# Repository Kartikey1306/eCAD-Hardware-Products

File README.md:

# eCAD Hardware Products

Hardware / PCB CAD design collection for the **EmbeddedOS (EoS)** ecosystem.
The repository organizes hardware product designs by application domain. Each
domain holds one or more product lines, and each product line typically carries
a product datasheet, a bill of materials (`bom.csv`), power-budget simulation
scripts, and placeholder directories for PCB and mechanical CAD artifacts.
Several product lines also include KiCad schematics (`*.kicad_sch`).

> Status varies by design. Directories are at different maturity levels (many
> "Design" / "Pre-production"); PCB and CAD folders often contain `.gitkeep`
> placeholders rather than finished layouts. Check each design's own `README.md`
> and `docs/` for its current state.

## Domains

The repository contains **16** domain design collections:

| Domain | Focus |
|---|---|
| `eAerospace_CAD_Design` | Aircraft components, avionics, UAV/drone systems, space systems |
| `eConsumer_CAD_Design` | Smart home devices, personal wearables, AR/smart devices |
| `eCybersecurity_CAD_Design` | Security appliances and physical security systems |
| `eDefense_CAD_Design` | Surveillance, tactical communications, protection equipment |
| `eElectronics_CAD_Design` | PCBs, embedded controllers, RF modules, FPGAs, AI accelerators |
| `eEnergy_CAD_Design` | Battery products, renewable energy systems, power electronics |
| `eHealth365_CAD_Design` | Two-device health monitoring system (smart patch / smart ring) |
| `eIndustrial_CAD_Design` | Sensors, industrial electronics, infrastructure equipment |
| `eMedical_CAD_Design` | Diagnostic, surgical, patient-care, laboratory equipment |
| `eMining_CAD_Design` | Autonomous mining/construction equipment, industrial safety systems |
| `ePAM_CAD_Design` | Personal air/ground mobility — solar-hybrid transport, 4-product line |
| `eRadar360_CAD_Design` | 360° automotive safety radar + laser + V2X + AI threat detection |
| `eRobotics_CAD_Design` | Industrial robots, autonomous systems, robot components |
| `eSmartCity_CAD_Design` | Urban infrastructure, utilities, telecommunications |
| `eTransport_CAD_Design` | Automotive electronics, rail systems, maritime systems |
| `eosHealth_CAD_Design` | Four-device wearable health platform |

Plus:

- `future_designs/` — early/prospective concepts (e.g. `eBCI-Lite`)
- `docs/` — repository-level documentation

## Typical design layout

Most domains follow a common structure, for example:

```
eAerospace_CAD_Design/
  README.md
  docs/                      business_plan.md, regulatory_path.md
  ebuild_simulation/         eBuild simulation notes
  <product_line>/
    product_datasheet.md
    bom.csv
    simulation/power_budget_sim.py
    hardware/
      pcb/  cad/  antenna/   (artifact folders; often .gitkeep placeholders)
```

Artifact formats present in the repo include Markdown datasheets, CSV BOMs,
Python simulation scripts, and KiCad schematics (`*.kicad_sch`). Some product
lines also include TypeScript/Dart companion app sources and 3D-model notes.

## Simulations

Power-budget simulations are plain Python scripts, runnable per product line:

```bash
cd eAerospace_CAD_Design/<product_line>/simulation/
python3 power_budget_sim.py
```

Design docs reference the [EoSim](https://github.com/embeddedos-org/EoSim)
digital-twin platform for hardware-in-the-loop testing. Running one script alone
does not establish that a product is validated.

## Evidence-backed product validation

The committed `tools/catalog/product_inventory.json` is the complete product
execution set. The v1 contract schemas and policy requirements are documented in
`docs/hardware-validation-contract-v1.md`.

Discover inventory drift and inspect local tool capabilities:

```bash
python3 tools/validate_products.py discover
python3 tools/validate_products.py capabilities
```

Execute V0-V4 for every inventoried product and write hash-bound receipts:

```bash
python3 tools/validate_products.py validate \
  --all \
  --output /tmp/ecad-validation \
  --mode evidence
python3 tools/validate_products.py verify-bundle \
  /tmp/ecad-validation/bundle.json
```

`--mode evidence` succeeds when the selected inventory was executed and valid
receipts were written. Individual products may still be honestly `FAIL`,
`BLOCKED`, `INCONCLUSIVE`, or `NOT_RUN`. Use `--mode gate` for a release check;
it succeeds only when every selected product has real `PASS` evidence for V0,
V1, V2, V3, and V4. Historical baseline entries never waive a failed or missing
requirement.

## CAD dataset and engineering model

`datasets/cad/` holds CAD dataset items for the multi-domain validation work
in issue #27. Each item is a STEP design, the design intent the CAD cannot
carry, and machine-readable requirements; the pipeline extracts it with the
OpenCASCADE kernel, builds an engineering model in which every value states
its source and status, and runs V0-V4 with domain simulators. `UNKNOWN`
values are never filled in: a requirement that depends on one is `BLOCKED`.

```bash
python3 -m pip install -r tools/requirements.txt -r tools/requirements-cad.txt
python3 tools/cad_dataset.py check    datasets/cad/robotic_joint_001
python3 tools/cad_dataset.py validate datasets/cad/robotic_joint_001 --output /tmp/joint-run
```

See [datasets/cad/README.md](datasets/cad/README.md) and
[docs/cad-dataset-engineering-model-v1.md](docs/cad-dataset-engineering-model-v1.md).

## License

MIT — see [LICENSE](LICENSE).

One exception: the EmbeddedOS original boards in [boards/eos](boards/eos), their design
files and the footprint library drawn for them are Copyright (c) 2026 Kartikeydheer Srivastava,
all rights reserved, and are not under the MIT licence. The exact files are listed in
[boards/eos/README.md](boards/eos/README.md#licence).

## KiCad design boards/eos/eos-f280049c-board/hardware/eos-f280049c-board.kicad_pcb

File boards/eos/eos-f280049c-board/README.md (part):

# EoS F280049C Board

A development board for the TI TMS320F280049C (C2000 real-time MCU, LQFP-100) with two
BoosterPack-compatible (40-pin) sites, 58.42 × 156.21 mm, four layers.
Designed by Kartikeydheer Srivastava. All rights reserved: not open source, and not under this repository's MIT licence.
Anyone may view it, clone this repository and run its tests; anything more needs
Kartikeydheer Srivastava's written permission (kartikeydheer@gmail.com). EmbeddedOS (EoS) Research Foundation has a limited, revocable
permission. See [LICENSE.txt](LICENSE.txt) and [the licence summary](../README.md#licence).

A board for the same job as TI's LAUNCHXL-F280049C LaunchPad; an original design, not a copy: no
file of the vendor's was used. "BoosterPack" names TI's plug-in module format to say which modules
fit (nominative use); this board is not a TI product. No design file of the vendor's was used; the header positions come from TI's BoosterPack Pinout Standard (updated Sept 1, 2013) and the 40-pin figure of TI's
BoosterPack Standards and Design Guide (processors.wiki.ti.com, archived 2017-11-03). TI's design
guide SPRACZ9A reproduces one circuit of the LaunchPad (its Figure 3-5, a CAN transceiver); that
figure was not used, and this board has no CAN transceiver. Every circuit value comes from the
chip makers' data sheets listed below.

| | |
|---|---|
|  |  |

## What is on it

| Block | What and why | Source |
|---|---|---|
| TMS320F280049C | C28x at 100 MHz with FPU, TMU and CLA, 256 KB flash, three 12-bit ADCs, LQFP-100 (PZ). KiCad's `LQFP-100_14x14mm_P0.5mm` footprint: TI's PZ0100A drawing gives a 14 × 14 mm body, 15.8–16.2 mm across the leads, 0.5 mm pitch, 1.6 mm maximum height (JEDEC MS-026) and 1.5 × 0.3 mm example pads on a 15.4 mm row pitch; KiCad's 1.6 × 0.3 mm pads on 15.35 mm cover that land. Turned 270° so its analog pins face both sites' analog header pins and its GPIO sides face the right-hand headers and the bottom. | TI SPRS945H (data sheet), Table 5-1, Figure 5-1, PZ0100A |
| Core supply | Internal VREG: VREGENZ tied straight to VSS, so a single 3.3 V supply runs the chip; the guide calls this the cost-effective choice for a small board. The internal DC-DC is not used (it needs a 2.2 µH inductor and 20 µF on VDDIO_SW, costs GPIO22/23, and the guide warns of ADC noise). 4.7 µF X7R 25 V 1206 (Murata GRM31CR71E475KA88L) at each of the four VDD pins: 18.8 µF nominal, with the modeled effective-capacitance margin described below; CVDD = 12–27 µF total and 0.1–6.75 µF per pin ("Configuration 1"); each VDD pin with its capacitor is its own net, which the data sheet allows in internal VREG mode. | SPRS945H 6.9.1.2.4–6.9.1.2.6, 6.9.1.3.1.2, 6.9.1.4.1, 6.9.1.5.1; TI SPRACZ9A 3.4.3 |
| 3.3 V pins | VDDIO, VDDA and VDDIO_SW on one 3.3 V rail, the inner layer 2 plane ("strongly recommended"; a separate VDDA "typically offers minimal benefits"). 0.1 µF at each VDDIO pin and at VDDIO_SW, 2.2 µF at each VDDA pin to VSSA. VSS_SW to VSS. | SPRS945H 6.9.1.4.1, 6.9.1.5.1, Table 5-1 |
| ADC references | Internal reference mode: 4.7 µF X7R 25 V 1206 (GRM31CR71E475KA88L) from VREFHIA (pin 25) to VREFLOA (pin 27) and from VREFHIB/C (pin 24) to VREFLOB/C (pin 26), at the chip's corner, each joined to both pins before the autorouter runs. Nothing else loads VREFHI. One ground plane (inner layer 1) for VSS and VSSA, since the analog lines arrive from header pins and a clean split is not possible. | SPRS945H Table 5-1; SPRACZ9A 3.3.3, 4.5 |
| 20 MHz clock | SiTime SiT8008BI-22-33N-20.000000E, a 3.3 V CMOS oscillator (±25 ppm with aging and temperature, 45–55 % duty, ≤ 2 ns rise/fall), into X1 in single-ended mode, X2 open, 0.1 µF at its supply. X1 accepts 2–20 MHz from an oscillator with ≤ 6 ns edges and 45–55 % duty. Not the internal oscillators: ±3 % over voltage and temperature, where the guide asks for an external source for CAN and for better than 1 %. Not a crystal: the data sheet asks for a crystal rated ≥ 1 mW of drive (or a damping resistor to be evaluated with the crystal), ESR ≤ 45–50 Ω and a 6–12 pF load at 20 MHz; the stocked SMD crystals with that ESR and load are rated 100 µW, and the 1 mW HC-49 parts are stocked with an 18 pF load, which would need 26–30 pF per side against the 24 pF limit. | SPRS945H 6.9.3.2.1, 6.9.3.4.4, 6.9.3.4.7, 6.9.3.5.1, Figure 6-17, Table 5-10; SPRACZ9A 3.2.4, 3.6.1; SiT8008B data sheet rev 1.08 |
| Reset | 2.2 kΩ pull-up and 100 nF on XRSn (2.2–10 kΩ, ≤ 100 nF so the watchdog can still pull it low in 512 clock cycles), a reset button straight to ground; also on J2.16 and J6.56. | SPRS945H 6.9.2, Figure 6-12, Table 5-1; SPRACZ9A 3.5 |
| Boot mode | GPIO24 (boot pin 1) and GPIO32 (boot pin 0) each have a 10 kΩ pull-up and go to JP1: a shunt on 1-2 pulls GPIO24 to ground through 1 kΩ (0.3 V, under VIL = 0.8 V), on 3-4 GPIO32. No shunt: flash; 1-2: SCI boot through the USB bridge (SCIA on GPIO28/29); 3-4: CAN; both: parallel I/O. Both pins are site B chip selects, which a BoosterPack does not drive, as the guide asks of a boot pin used "as outputs whose state is irrelevant during boot". | SPRS945H Tables 7-13, 7-18, 6.6; SPRACZ9A 3.2.5 |
| JTAG (J10) | TI 14-pin header, 2 × 7 at 0.1 in with pin 6 as the key, in place of TI's on-board XDS110, whose firmware is TI's: 1 TMS (2.2 kΩ pull-up), 3 TDI and 7 TDO (10 kΩ pull-ups; their internal pull-ups are off by default), 11 TCK, 9 RTCK looped to TCK, 4 TDIS and 8/10/12 to ground with no resistor, 5 PD to 3.3 V through 100 Ω, 2 TRST open (the chip has no TRSTn pin), 13/14 EMU0/EMU1 pulled up with 4.7 kΩ. Any XDS-class probe connects here; the header is under 6 in from the chip, so no buffers. | TI XDS Target Connection Guide; TI SPRU655I Figure 4, Table 13; SPRS945H Table 5-1; SPRACZ9A 3.7.1, Figure 3-16 |
| USB-UART (J9) | CP2102N-A02-GQFN20 on SCIA (GPIO28 RX, GPIO29 TX), the default SCI boot pins, on the board's 3.3 V with its regulator unused, so it is powered whenever the MCU is and neither drives an unpowered chip. 4.7 µF + 0.1 µF on VREGIN and on VDD, each 0.1 µF at its pin; 1 kΩ RSTb pull-up; 1 kΩ in TXD and RXD; 10 kΩ pull-up on SCIA_RX. VBUS sense: the self-powered figure's 22.1 kΩ / 47.5 kΩ divider from the fused VBUS plus a 5.1 kΩ bleed, so the pin stays under VIL = 0.6 V unless more than 185 µA is pushed into VBUS; the Schottky's reverse leakage is 0.8 µA typical at 25 °C and about 0.1 mA typical at 85 °C. A guaranteed hot-leakage limit is not supplied, so unplug detection with externally supplied 5 V still needs a temperature test. The main USB pair runs from the receptacle's A6/A7 contacts through the ESD part's pads straight down into the CP2102N's D+/D− pins, on the top layer, laid before the autorouter; the duplicate B6/B7 contacts join afterward, with two vias in the B7 branch. | Silicon Labs CP2102N Rev. 1.5, Figures 2.3, 2.6, section 2.3, Tables 3.2, 3.7, 3.10; SPRS945H Table 7-18; SPRACZ9A 3.2.4; Nexperia PMEG6010CEH v.4 |
| USB ESD, USB-C | Littelfuse SP0503BAHTG at the connector: three TVS diodes to ground on VBUS, D+ and D−, 5.5 V standoff, ≤ 100 nA at 5 V, 30 pF; it has no path from D+/D− into VBUS, so a D+ pull-up left on cannot hold VBUS up after a host leaves. USB-C as a 5 V sink: 5.1 kΩ Rd on CC1 and CC2. | Littelfuse SP05xxBA; CP2102N Figure 2.5; TI SLYY228 p. 54 |
| Power | USB VBUS → 500 mA polyfuse (0.42 A hold at 40 °C) → PMEG6010CEH Schottky → +5V, which feeds both sites' 5 V pins and the AP7361C-33 LDO (1 A, current limit ≥ 1.1 A, 4.7 µF in, 10 µF out). The Schottky stops a BoosterPack that drives 5 V into J3.21 or J7.61 from back-feeding the USB host; that BoosterPack then powers the board. Design allowance for the 3.3 V load: the MCU's 113 mA + 30 mA (IDDIO + IDDA maxima with the internal VREG), the CP2102N 14 mA, the oscillator 4.5 mA, LEDs and pull-ups about 12 mA: about 175 mA, 263 mA with the guide's 1.5 margin, well inside the LDO's 1 A; its minimum current limit exceeds the VREG's 650 mA typical turn-on inrush. Startup under this load has not been measured: the LDO's 150 µs typical startup figure uses a different load and capacitance, so it does not establish the board's ramp rate. Green power LED at 2.1 mA. | SPRS945H 6.5.2, 6.9.1.5.1–6.9.1.5.2; SPRACZ9A 3.4.5; Diodes DS37274 Rev. 5-2; Littelfuse 1206L; Nexperia PMEG6010CEH v.4; Kingbright DSAO7432 |
| Shared power budget | The LDO may carry 300 mA: at 5.25 V in it dissipates 0.59 W, 64 °C above ambient at 110 °C/W. So the BoosterPacks may take 125 mA from the 3.3 V pins (J1.1 and J5.41 together). In all, the board takes up to 0.38 A from USB: 175 mA for itself, 200 mA for the BoosterPacks' 3.3 V and 5 V pins together (no more than 125 mA of it on 3.3 V), 1 mA for the bleed: under the polyfuse's 0.42 A hold at 40 °C and a configured 500 mA USB supply. This thermal budget does not establish USB attach or suspend compliance. At 0.38 A and 4.75 V from the host, the fuse (0.70 Ω) and Schottky (≤ 0.53 V) leave ≥ 3.95 V on +5V: the LDO keeps regulating, but the 5 V pins carry 3.95–4.9 V, not a regulated 5 V. The Schottky then dissipates ≤ 0.2 W, 66 °C above ambient on its standard footprint. J1.1 and J5.41 are outputs only. | DS37274 (p. 4 absolute maximum, p. 5 θJA, dropout); Littelfuse 1206L derating table; PMEG6010CEH Tables 5–7 |
| User LEDs, buttons | Red LED on GPIO6 (J4.40) and yellow on GPIO14 (J4.39), both PWM outputs, through 680 Ω: 2.3 and 2.1 mA. Buttons on GPIO23 (J2.11/J6.51, 10 kΩ pull-up because of its 45 µA leakage) and GPIO11 (J2.17/J6.57, internal pull-up), each through 1 kΩ because the pins also reach the BoosterPacks; a reset button. | Kingbright DSAO7433, DSAO7434; SPRS945H 6.6, Table 5-1 |
| I2C pull-ups | 2.2 kΩ on SDA and SCL: above RP(min) = 0.97 kΩ, fast mode up to 161 pF. | SPRACZ9A 3.2.4; TI SLVA689A Eq. 1, 6, Table 2-1 |
| BoosterPack headers | Samtec SSW-110-23-F-D, female with long male leads, so the board stays usable under a stack of BoosterPacks. | TI BoosterPack Pinout Standard (Sept 1, 2013) p. 2 |

### BoosterPack pin map

Each site follows TI's 40-pin standard: 0.1 in grid, outer headers 1.8 in apart, inner 1.6 in,
pin-1 rows level. The sites sit one above the other, 2.5 in (63.50 mm) apart, so two BoosterPacks fit at once
(each reaches 350 mil above its pin 1 and 0.15 in below its last row). Site B's headers are named
J5 (as J1), J7 (as J3), J8 (as J4) and J6 (as J2), with pins numbered 40 above site A's. The chip
has 35 GPIOs free for 50 digital positions, so the sites share the buses the standard says can be
shared (SPI and I2C) and some GPIO positions; a shared position joins site A pin n to site B pin
n + 40. Each site keeps its own UART, PWMs and chip selects. Mux positions from data sheet Table 5-6.

| Pin | Standard | Site A | | Pin | Standard | Site B |
|---|---|---|---|---|---|---|
| J1.1 | 3.3 V | +3V3 (output) | | J5.41 | 3.3 V | +3V3 (output) |
| J1.2 | analog | B3 | | J5.42 | analog | B4/C8 |
| J1.3 | UART RX (into the MCU) | GPIO59 / LINA_RX | | J5.43 | UART RX | GPIO13 / SCIB_RX |
| J1.4 | UART TX | GPIO22 / LINA_TX | | J5.44 | UART TX | GPIO12 / SCIB_TX |
| J1.5 | GPIO | GPIO33, shared | | J5.45 | GPIO | GPIO33, shared |
| J1.6 | analog | C0 | | J5.46 | analog | C3 |
| J1.7 | SPI CLK | GPIO56 / SPIA_CLK, shared | | J5.47 | SPI CLK | GPIO56, shared |
| J1.8 | GPIO | GPIO16, shared | | J5.48 | GPIO | GPIO16, shared |
| J1.9 | I2C SCL | GPIO27 / I2CA_SCL, shared | | J5.49 | I2C SCL | GPIO27, shared |
| J1.10 | I2C SDA | GPIO26 / I2CA_SDA, shared | | J5.50 | I2C SDA | GPIO26, shared |
| J3.21 | 5 V | +5V | | J7.61 | 5 V | +5V |
| J3.22 | GND | GND | | J7.62 | GND | GND |
| J3.23–J3.28 | analog | A2, A3, C4, C2, A1/DACB_OUT, A0/DACA_OUT | | J7.63–J7.68 | analog | A9, A8, A4, A5, C1, C5 |
| J3.29, J3.30 | reserved | not connected | | J7.69, J7.70 | reserved | not connected |
| J4.40 | PWM | GPIO6 / EPWM4A (red LED) | | J8.80 | PWM | GPIO3 / EPWM2B |
| J4.39 | PWM | GPIO14 / EPWM8A (yellow LED) | | J8.79 | PWM | GPIO2 / EPWM2A |
| J4.38 | PWM | GPIO9 / EPWM5B | | J8.78 | PWM | GPIO0 / EPWM1A |
| J4.37 | PWM | GPIO5 / EPWM3B | | J8.77 | PWM | GPIO7 / EPWM4B |
| J4.36, J4.35 | timer capture | GPIO31, GPIO17 (eCAP through the Input X-BAR), shared | | J8.76, J8.75 | timer capture | shared |
| J4.34–J4.31 | GPIO | GPIO4, GPIO58, GPIO57, GPIO25, shared | | J8.74–J8.71 | GPIO | shared |
| J2.20 | GND | GND | | J6.60 | GND | GND |
| J2.19 | PWM | GPIO15 / EPWM8B | | J6.59 | PWM | GPIO1 / EPWM1B |
| J2.18 | SPI CS (wireless) | GPIO34 | | J6.58 | SPI CS (wireless) | GPIO40 |
| J2.17 | GPIO** | GPIO11, shared (button SW3) | | J6.57 | GPIO** | shared |
| J2.16 | RST | XRSn | | J6.56 | RST | XRSn |
| J2.15 | SPI MOSI | GPIO8 / SPIA_SIMO, shared | | J6.55 | SPI MOSI | shared |
| J2.14 | SPI MISO | GPIO10 / SPIA_SOMI, shared | | J6.54 | SPI MISO | shared |
| J2.13 | SPI CS (display) | GPIO39 | | J6.53 | SPI CS (display) | GPIO24 (boot pin 1, 10 kΩ pull-up) |
| J2.12 | SPI CS (other) | GPIO30 | | J6.52 | SPI CS (other) | GPIO32 (boot pin 0, 10 kΩ pull-up) |
| J2.11 | GPIO | GPIO23, shared (button SW2) | | J6.51 | GPIO | shared |

Notes for firmware and BoosterPack designers:

- **Clock:** the 20 MHz oscillator drives X1 single-ended: set XTALCR.SE = 1 (data sheet
  Figure 6-17). Keep GPIO19 in input mode with its pull-up disabled (Table 5-1). The chip starts on INTOSC2.
- **Site A's UART is LIN-A** in its SCI-compatible mode (the data sheet lists it as a
  "UART-Compatible Local Interconnect Network"); site B's is SCI-B. SCI-A is the USB bridge.
- **GPIO22** comes out of reset in DC-DC mode: clear its GPAAMSEL bit, with DCDCCTL.DCDCEN left
  at 0, before using it as LINA_TX (Table 5-1).
- **GPIO23** has about 100 pF of internal capacitance and up to 45 µA of leakage (Table 5-1,
  section 6.6): it suits the button and slow signals, not fast edges.
- **Boot pins:** a BoosterPack must not pull J6.53 (GPIO24) or J6.52 (GPIO32) low at reset, or the
  chip boots in another mode. The 10 kΩ pull-ups keep both chip selects high until firmware runs.
- **Shared positions:** a shared GPIO, capture input or bus line reaches both sites; two
  BoosterPacks must not both drive one.
- **The buttons** need GPIO11's internal pull-up enabled (GPIO23 has its own 10 kΩ).
- **Power on the 3.3 V pins (J1.1, J5.41):** outputs only, 125 mA for both sites together; never
  feed them. The 5 V pins may be fed by a BoosterPack (the Schottky keeps that 5 V off USB).
- The analog pins A6, B2/C6, A10, B0, C14 and the PGAx_IN-only pins are not connected
  (Table 5-10 allows it); the five PGAx_GND pins are tied to VSSA.

## Not on this board

- **TI's on-board XDS110 debug probe.** Its firmware is TI's, so it is replaced by the standard TI
  14-pin JTAG header (J10) for an external XDS110, XDS200 or similar probe, and a separate USB-UART
  bridge (CP2102N) for the serial port and SCI boot.
- **A CAN transceiver, and any other interface transceiver.** The CAN lines are free GPIOs; a
  BoosterPack with a transceiver can use CAN-A or CAN-B through the pin mux.
- **A crystal.** An oscillator drives X1 instead (see the clock row above).
- **External 1.2 V supply and the internal DC-DC.** The internal LDO VREG makes the core supply.
- **An external ADC reference.** The chip's internal reference drives VREFHI; the guide's
  external-reference circuit (REF3030 plus an op-amp) is not fitted.
- **Pull resistors on the PWM outputs and on four of the six chip selects.** SPRACZ9A 3.2.1 says
  PWM lines and chip selects "should have external pull-resistors to enforce a state during
  power-up", since the GPIOs float until firmware runs; only GPIO24 and GPIO32 (boot pins, site B
  chip selects) have them here. A BoosterPack whose PWM or chip-select inputs must be held at
  power-up brings its own.
- **ESD parts on the BoosterPack lines:** the headers are a board-to-board connection.
- The vendor schematic, PCB, Gerber and BOM files were not opened. SPRUII7B was used only for published mechanical facts (Table 1 and Figure 12).

## Mechanical compatibility

The outline is 58.42 × 156.21 mm (2300 × 6150 mil), with 1.27 mm (50 mil) corner radii,
from TI SPRUII7B Table 1 and Figure 12. Coordinates below are measured from the upper-left
corner; internal component placement and electrical routing are independently designed.

| Feature | Position |
|---|---|
| Outer BoosterPack columns | x = 6.35 and 52.07 mm (250 and 2050 mil) |
| Inner columns | x = 8.89 and 49.53 mm (350 and 1950 mil) |
| Site A first row | y = 50.80 mm (2000 mil) |
| Site B first row | y = 114.30 mm (4500 mil); 63.50 mm between sites |
| Four mounting-hole centres | 2.54 mm (100 mil) from their two adjacent edges |
| Mounting-hole drill | 3.2 mm non-plated M3 clearance; intentionally 0.152 mm larger than the published 120 mil (3.048 mm) nominal |

The two header patterns and overall footprint match those published dimensions. This is not
an enclosure-fit or plug-stack qualification: the USB-C connector replaces micro-USB, debug
and boot connectors are independently placed, and no physical fit has been tested. The
mounting holes are unplated; M3 heads/washers can overhang the edge, as the 2.54 mm corner
centre offset is smaller than a typical screw-head radius.

## Core and reference capacitor margin

C10/C17/C20/C22 (core) and C14/C15 (references) use Murata GRM31CR71E475KA88L,
4.7 µF ±10 %, X7R, 25 V, 1206. Murata's public SimSurfing model was sampled on 2026-10-15
at 10 mVrms, −40 to +125 °C in 5 °C steps. The core sweep from 0 to 1.375 V gives
4.022–4.562 µF; the more conservative reference sweep from 0 to 3.625 V gives at least
3.898 µF. Applying −10 % initial tolerance and a further 10 % design reserve yields at least
3.258 µF per core pin (13.03 µF total, above the required 12 µF) and 3.157 µF per reference
(above the required 2.2 µF). On the high side, nominal capacitance ×1.10 tolerance ×1.15
X7R variation is 5.946 µF per core pin and 23.78 µF total, below 6.75/27 µF.

These are manufacturer-model results with explicit engineering reserve, not guaranteed
production minima or qualification of the board over that temperature range. Verify the
procured capacitors at operating DC bias, small AC amplitude, temperature and age before
production; the extra 10 % reserve is not a manufacturer aging specification. The internal
reference's settling time with 4.7 µF also needs bring-up verification. VDDA's C13/C16 remain
2.2 µF nominal: SPRS945H 6.9.1.5.1 gives CVDDA as **typical**, whereas Table 5-1 explicitly
requires **at least** 2.2 µF at VREFHI. The earlier 0603 core and nominal 2.2 µF reference
choices were replaced because they did not demonstrate the required effective minimum.

## Build results

The numbers below are from `build-report.json` and `drc.json` in this folder.

| Check | Result |
|---|---|
| Schematic ERC | 0 violations |
| DRC errors | 0 |
| Unconnected items | 0 |
| Schematic ↔ board parity | 0 differences |
| DRC warnings | 2: silkscreen within the board-edge clearance, the outline of J9 (USB-C), which sits at the board edge |

## Fabrication

4 layers, 1.6 mm thick: top signal, inner 1 ground, inner 2 3.3 V, bottom signal; ground also
poured on both outer layers. TI's guide: "A 4-layer board or more is often the best choice for
C2000 devices. This enables the designer to include a clean ground plane and split power plane"
(SPRACZ9A 4.1.3), and it asks for an unbroken ground plane (4.4). Here the analog lines run from
header pins and need that return under them, and 80 header pins plus the LQFP-100's 18 supply
pins on four sides would leave no clean ground on two layers. Design rules: 0.15 mm clearance;
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
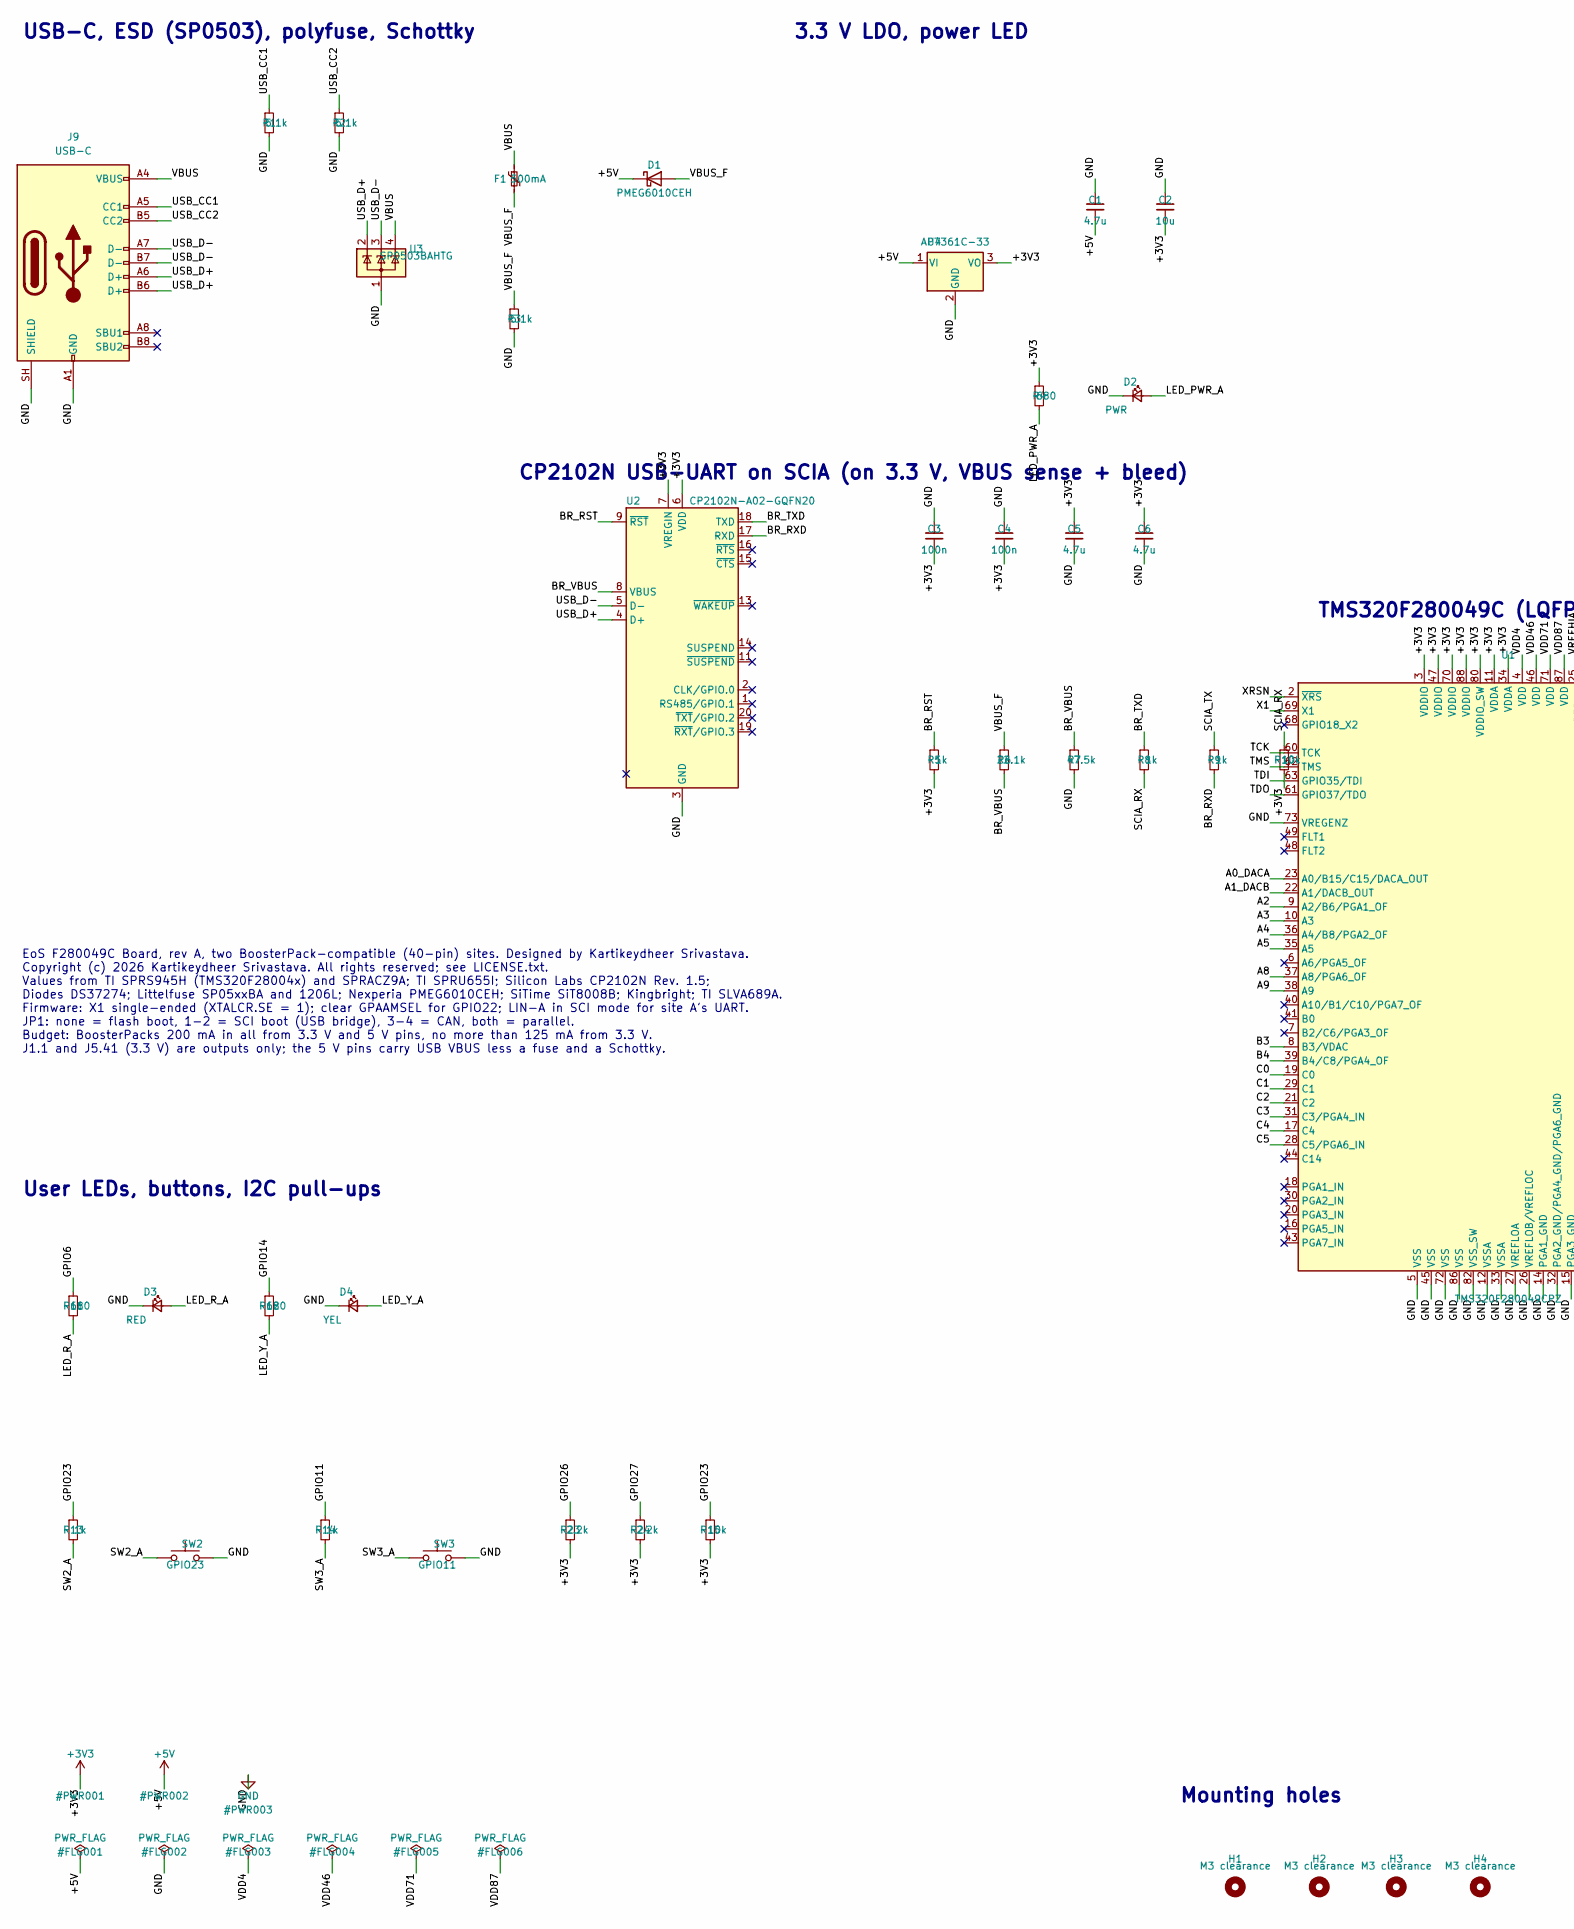
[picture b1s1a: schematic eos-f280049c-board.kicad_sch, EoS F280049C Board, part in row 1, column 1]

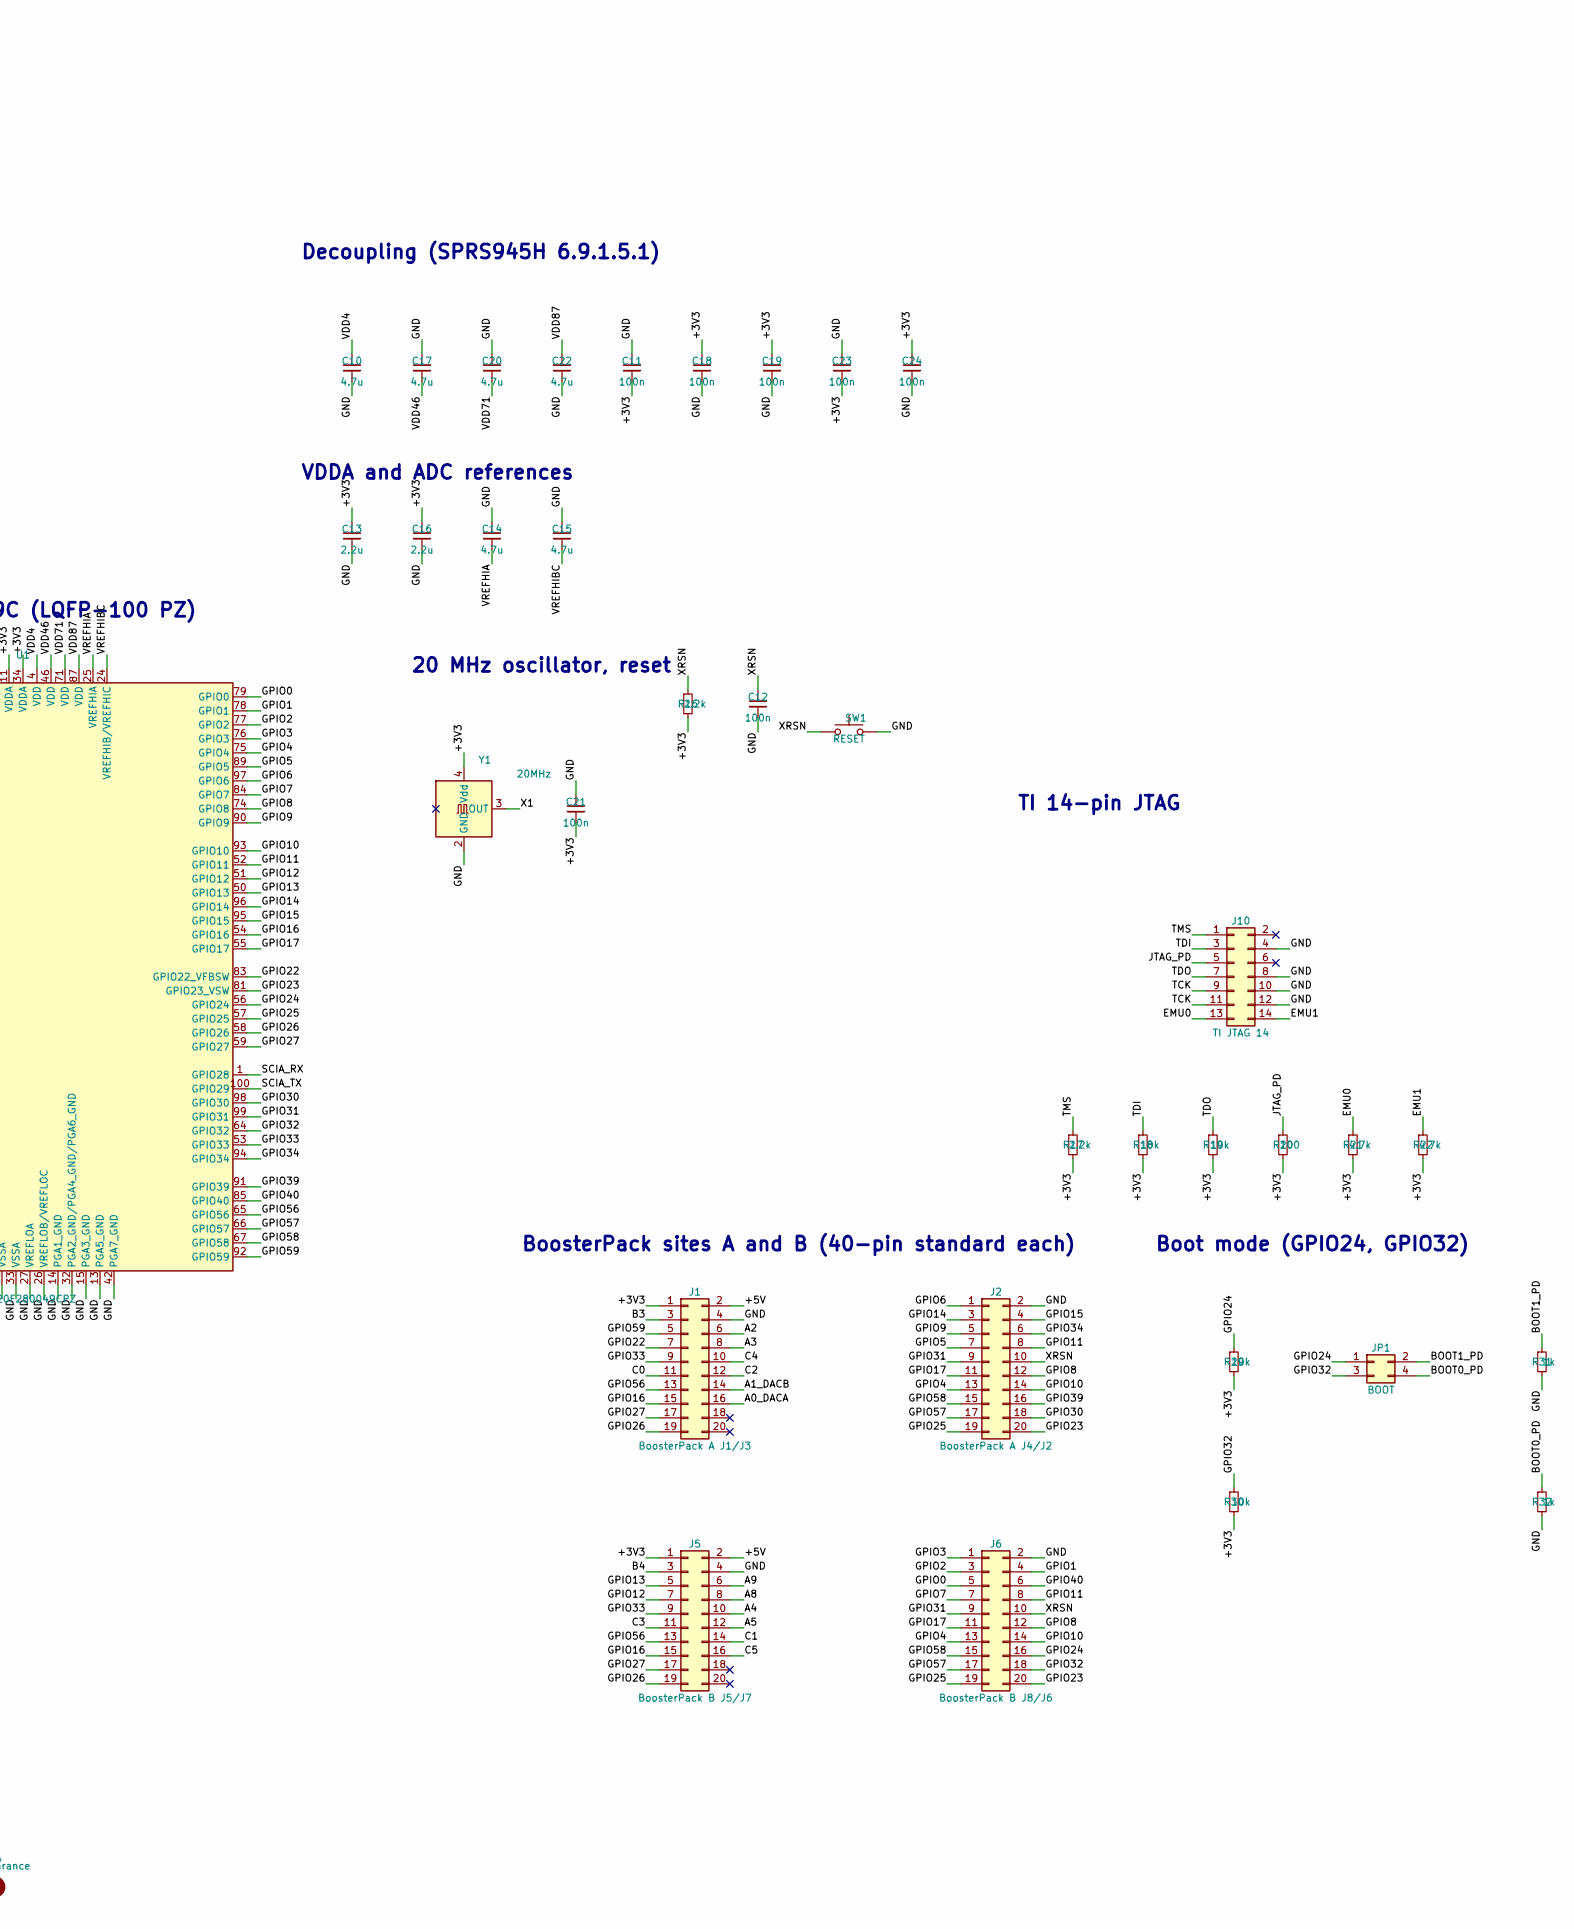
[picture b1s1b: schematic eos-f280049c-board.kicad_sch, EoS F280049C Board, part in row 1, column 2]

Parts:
C1: 4.7u; C_0805_2012Metric; MPN GRM21BR61A475KA73L
C2: 10u; C_0805_2012Metric; MPN GRM21BR61A106KE19L
C3, C4, C11, C12, C18, C19, C21, C23, C24: 100n; C_0402_1005Metric; MPN GRM155R71C104KA88D
C5, C6: 4.7u; C_0603_1608Metric; MPN GRM188R61A475KE15D
C10, C14, C15, C17, C20, C22: 4.7u; C_1206_3216Metric; MPN GRM31CR71E475KA88L
C13: 2.2u; C_0603_1608Metric; MPN GRM188R71A225KE15D
C16: 2.2u; C_0402_1005Metric; MPN GRM155R61A225KE01D
D1: PMEG6010CEH; D_SOD-123F; MPN PMEG6010CEH,115
D2: PWR; LED_0603_1608Metric; MPN APTD1608LCGCK
D3: RED; LED_0603_1608Metric; MPN APTD1608LSURCK
D4: YEL; LED_0603_1608Metric; MPN APTD1608LSYCK
F1: 500mA; Fuse_1206_3216Metric; MPN 1206L050YR
H1, H2, H3, H4: M3 clearance; MountingHole_3.2mm_M3
J1: BoosterPack A J1/J3; PinHeader_2x10_P2.54mm_Vertical; MPN SSW-110-23-F-D
J2: BoosterPack A J4/J2; PinHeader_2x10_P2.54mm_Vertical; MPN SSW-110-23-F-D
J5: BoosterPack B J5/J7; PinHeader_2x10_P2.54mm_Vertical; MPN SSW-110-23-F-D
J6: BoosterPack B J8/J6; PinHeader_2x10_P2.54mm_Vertical; MPN SSW-110-23-F-D
J9: USB-C; USB_C_Receptacle_HRO_TYPE-C-31-M-12; MPN TYPE-C-31-M-12
J10: TI JTAG 14; PinHeader_2x07_P2.54mm_Vertical; MPN TSW-107-07-G-D
JP1: BOOT; PinHeader_2x02_P2.54mm_Vertical; MPN TSW-102-07-G-D
R1, R2, R3: 5.1k; R_0402_1005Metric
R4, R11, R12: 680; R_0402_1005Metric
R5, R8, R9, R13, R14, R31, R32: 1k; R_0402_1005Metric
R6: 22.1k; R_0402_1005Metric
R7: 47.5k; R_0402_1005Metric
R10, R15, R18, R19, R29, R30: 10k; R_0402_1005Metric
R16, R17, R23, R24: 2.2k; R_0402_1005Metric
R20: 100; R_0402_1005Metric
R21, R22: 4.7k; R_0402_1005Metric
SW1: RESET; SW_Push_1P1T_NO_CK_KMR2; MPN KMR221G LFS
SW2: GPIO23; SW_Push_1P1T_NO_CK_KMR2; MPN KMR221G LFS
SW3: GPIO11; SW_Push_1P1T_NO_CK_KMR2; MPN KMR221G LFS
U1: TMS320F280049CPZ; LQFP-100_14x14mm_P0.5mm; MPN F280049CPZS
U2: CP2102N-A02-GQFN20; SiliconLabs_QFN-20-1EP_3x3mm_P0.5mm_EP1.8x1.8mm; MPN CP2102N-A02-GQFN20R
U3: SP0503BAHTG; SOT-143; MPN SP0503BAHTG
U4: AP7361C-33; SOT-223-3_TabPin2; MPN AP7361C-33E-13
Y1: 20MHz; Oscillator_SMD_SiT_PQFN-4Pin_3.2x2.5mm; MPN SiT8008BI-22-33N-20.000000E

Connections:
+3V3: C2.2, C3.2, C4.2, C5.1, C6.1, C11.2, C13.1, C16.1, C18.1, C19.1, C21.2, C23.2, C24.1, J1.1, J5.1, R4.1, R5.2, R10.2, R15.2, R16.2, R17.2, R18.2, R19.2, R20.2, R21.2, R22.2, R23.2, R24.2, R29.2, R30.2, U1.3 (VDDIO), U1.11 (VDDA), U1.34 (VDDA), U1.47 (VDDIO), U1.70 (VDDIO), U1.80 (VDDIO_SW), U1.88 (VDDIO), U2.6 (VDD), U2.7 (VREGIN), U4.3 (VO), Y1.4 (Vdd)
+5V: C1.2, D1.1 (K), J1.2, J5.2, U4.1 (VI)
/A0_DACA: J1.16, U1.23 (A0/B15/C15/DACA_OUT)
/A1_DACB: J1.14, U1.22 (A1/DACB_OUT)
/A2: J1.6, U1.9 (A2/B6/PGA1_OF)
/A3: J1.8, U1.10 (A3)
/A4: J5.10, U1.36 (A4/B8/PGA2_OF)
/A5: J5.12, U1.35 (A5)
/A8: J5.8, U1.37 (A8/PGA6_OF)
/A9: J5.6, U1.38 (A9)
/B3: J1.3, U1.8 (B3/VDAC)
/B4: J5.3, U1.39 (B4/C8/PGA4_OF)
/BOOT0_PD: JP1.4, R32.1
/BOOT1_PD: JP1.2, R31.1
/BR_RST: R5.1, U2.9 (~RST)
/BR_RXD: R9.2, U2.17 (RXD)
/BR_TXD: R8.1, U2.18 (TXD)
/BR_VBUS: R6.2, R7.1, U2.8 (VBUS)
/C0: J1.11, U1.19 (C0)
/C1: J5.14, U1.29 (C1)
/C2: J1.12, U1.21 (C2)
/C3: J5.11, U1.31 (C3/PGA4_IN)
/C4: J1.10, U1.17 (C4)
/C5: J5.16, U1.28 (C5/PGA6_IN)
/EMU0: J10.13, R21.1
/EMU1: J10.14, R22.1
/GPIO0: J6.5, U1.79 (GPIO0)
/GPIO1: J6.4, U1.78 (GPIO1)
/GPIO2: J6.3, U1.77 (GPIO2)
/GPIO3: J6.1, U1.76 (GPIO3)
/GPIO4: J2.13, J6.13, U1.75 (GPIO4)
/GPIO5: J2.7, U1.89 (GPIO5)
/GPIO6: J2.1, R11.1, U1.97 (GPIO6)
/GPIO7: J6.7, U1.84 (GPIO7)
/GPIO8: J2.12, J6.12, U1.74 (GPIO8)
/GPIO9: J2.5, U1.90 (GPIO9)
/GPIO10: J2.14, J6.14, U1.93 (GPIO10)
/GPIO11: J2.8, J6.8, R14.1, U1.52 (GPIO11)
/GPIO12: J5.7, U1.51 (GPIO12)
/GPIO13: J5.5, U1.50 (GPIO13)
/GPIO14: J2.3, R12.1, U1.96 (GPIO14)
/GPIO15: J2.4, U1.95 (GPIO15)
/GPIO16: J1.15, J5.15, U1.54 (GPIO16)
/GPIO17: J2.11, J6.11, U1.55 (GPIO17)
/GPIO22: J1.7, U1.83 (GPIO22_VFBSW)
/GPIO23: J2.20, J6.20, R13.1, R15.1, U1.81 (GPIO23_VSW)
/GPIO24: J6.16, JP1.1, R29.1, U1.56 (GPIO24)
/GPIO25: J2.19, J6.19, U1.57 (GPIO25)
/GPIO26: J1.19, J5.19, R23.1, U1.58 (GPIO26)
/GPIO27: J1.17, J5.17, R24.1, U1.59 (GPIO27)
/GPIO30: J2.18, U1.98 (GPIO30)
/GPIO31: J2.9, J6.9, U1.99 (GPIO31)
/GPIO32: J6.18, JP1.3, R30.1, U1.64 (GPIO32)
/GPIO33: J1.9, J5.9, U1.53 (GPIO33)
/GPIO34: J2.6, U1.94 (GPIO34)
/GPIO39: J2.16, U1.91 (GPIO39)
/GPIO40: J6.6, U1.85 (GPIO40)
/GPIO56: J1.13, J5.13, U1.65 (GPIO56)
/GPIO57: J2.17, J6.17, U1.66 (GPIO57)
/GPIO58: J2.15, J6.15, U1.67 (GPIO58)
/GPIO59: J1.5, U1.92 (GPIO59)
/JTAG_PD: J10.5, R20.1
/LED_PWR_A: D2.2 (A), R4.2
/LED_R_A: D3.2 (A), R11.2
/LED_Y_A: D4.2 (A), R12.2
/SCIA_RX: R8.2, R10.1, U1.1 (GPIO28)
/SCIA_TX: R9.1, U1.100 (GPIO29)
/SW2_A: R13.2, SW2.1
/SW3_A: R14.2, SW3.1
/TCK: J10.9, J10.11, U1.60 (TCK)
/TDI: J10.3, R18.1, U1.63 (GPIO35/TDI)
/TDO: J10.7, R19.1, U1.61 (GPIO37/TDO)
/TMS: J10.1, R17.1, U1.62 (TMS)
/USB_CC1: J9.A5 (CC1), R1.1
/USB_CC2: J9.B5 (CC2), R2.1
/USB_D+: J9.A6 (D+), J9.B6 (D+), U2.4 (D+), U3.2 (K)
/USB_D-: J9.A7 (D-), J9.B7 (D-), U2.5 (D-), U3.3 (K)
/VBUS: F1.1, J9.A4 (VBUS), J9.A9 (VBUS), J9.B4 (VBUS), J9.B9 (VBUS), U3.4 (K)
/VBUS_F: D1.2 (A), F1.2, R3.1, R6.1
/VDD4: C10.1, U1.4 (VDD)
/VDD46: C17.2, U1.46 (VDD)
/VDD71: C20.2, U1.71 (VDD)
/VDD87: C22.1, U1.87 (VDD)
/VREFHIA: C14.2, U1.25 (VREFHIA)
/VREFHIBC: C15.2, U1.24 (VREFHIB/VREFHIC)
/X1: U1.69 (X1), Y1.3 (OUT)
/XRSN: C12.1, J2.10, J6.10, R16.1, SW1.1, U1.2 (~XRS)
GND: C1.1, C2.1, C3.1, C4.1, C5.2, C6.2, C10.2, C11.1, C12.2, C13.2, C14.1, C15.1, C16.2, C17.1, C18.2, C19.2, C20.1, C21.1, C22.2, C23.1, C24.2, D2.1 (K), D3.1 (K), D4.1 (K), J1.4, J2.2, J5.4, J6.2, J9.A1 (GND), J9.A12 (GND), J9.B1 (GND), J9.B12 (GND), J9.SH (SHIELD), J10.4, J10.8, J10.10, J10.12, R1.2, R2.2, R3.2, R7.2, R31.2, R32.2, SW1.2, SW2.2, SW3.2, U1.5 (VSS), U1.12 (VSSA), U1.13 (PGA5_GND), U1.14 (PGA1_GND), U1.15 (PGA3_GND), U1.26 (VREFLOB/VREFLOC), U1.27 (VREFLOA), U1.32 (PGA2_GND/PGA4_GND/PGA6_GND), U1.33 (VSSA), U1.42 (PGA7_GND), U1.45 (VSS), U1.72 (VSS), U1.73 (VREGENZ), U1.82 (VSS_SW), U1.86 (VSS), U2.3 (GND), U2.12 (GND), U2.21 (GND), U3.1 (A), U4.2 (GND), Y1.2 (GND)

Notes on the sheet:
USB-C, ESD (SP0503), polyfuse, Schottky
3.3 V LDO, power LED
CP2102N USB-UART on SCIA (on 3.3 V, VBUS sense + bleed)
TMS320F280049C (LQFP-100 PZ)
Decoupling (SPRS945H 6.9.1.5.1)
VDDA and ADC references
20 MHz oscillator, reset
TI 14-pin JTAG
Boot mode (GPIO24, GPIO32)
BoosterPack sites A and B (40-pin standard each)
User LEDs, buttons, I2C pull-ups
Mounting holes
EoS F280049C Board, rev A, two BoosterPack-compatible (40-pin) sites. Designed by Kartikeydheer Srivastava. Copyright (c) 2026 Kartikeydheer Srivastava. All rights reserved; see LICENSE.txt. Values from TI SPRS945H (TMS320F28004x) and SPRACZ9A; TI SPRU655I; Silicon Labs CP2102N Rev. 1.5; Diodes DS3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

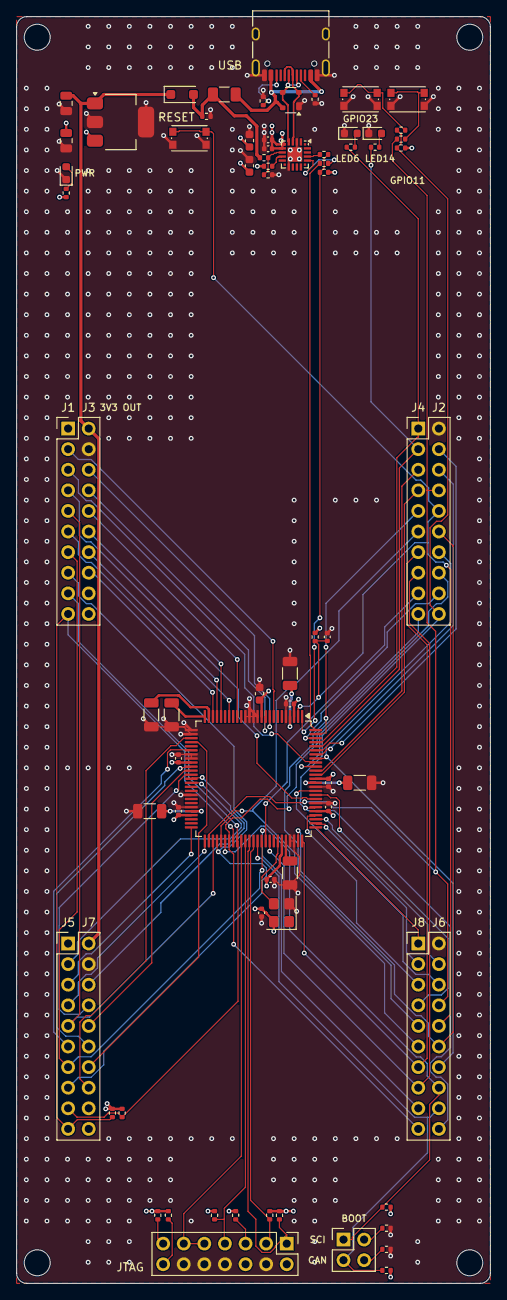
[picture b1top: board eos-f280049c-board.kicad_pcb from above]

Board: 4 copper layers, 58.4 x 156.2 mm, 73 parts (0 on the bottom side), 88 nets.

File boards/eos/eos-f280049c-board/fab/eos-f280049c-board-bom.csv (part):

"Refs","Value","Footprint","Manufacturer","MPN","Description","Qty","DNP"
"C1","4.7u","Capacitor_SMD:C_0805_2012Metric","Murata","GRM21BR61A475KA73L","Capacitor 4.7 uF X5R 10 V 0805, LDO input (DS37274: >= 1 uF)","1",""
"C2","10u","Capacitor_SMD:C_0805_2012Metric","Murata","GRM21BR61A106KE19L","Capacitor 10 uF X5R 10 V 0805, LDO output (DS37274: >= 2.2 uF ceramic; more helps load transients, as the MCU's 650 mA VREG inrush, SPRS945H 6.9.1.5.2)","1",""
"C3,C4,C11,C12,C18,C19,C21,C23,C24","100n","Capacitor_SMD:C_0402_1005Metric","Murata","GRM155R71C104KA88D","Capacitor 100 nF X7R 16 V 0402, CP2102N VDD (pin 6), at the pin (Silicon Labs CP2102N data sheet Rev. 1.5 Figure 2.3),Capacitor 100 nF X7R 16 V 0402, CP2102N VREGIN (pin 7), at the pin (Silicon Labs CP2102N data sheet Rev. 1.5 Figure 2.3),Capacitor 100 nF X7R 16 V 0402, VDDIO pin 3 to VSS pin 5 (CVDDIO_DECAP 0.1 uF, TI SPRS945H 6.9.1.5.1),Capacitor 100 nF X7R 16 V 0402, VDDIO pin 47 to VSS pin 45 (TI SPRS945H 6.9.1.5.1),Capacitor 100 nF X7R 16 V 0402, VDDIO pin 70 (TI SPRS945H 6.9.1.5.1),Capacitor 100 nF X7R 16 V 0402, VDDIO pin 88 to VSS pin 86 (TI SPRS945H 6.9.1.5.1),Capacitor 100 nF X7R 16 V 0402, VDDIO_SW pin 80 to VSS_SW pin 82 (CVDDIO_SW 0.1 uF, LDO only, TI SPRS945H 6.9.1.5.1),Capacitor 100 nF X7R 16 V 0402, XRSn filter: 100 nF or smaller (TI SPRS945H 6.9.2, Table 5-1),Capacitor 100 nF X7R 16 V 0402, oscillator VDD (SiT8008B: 0.1 uF or more is required)","9",""
"C5,C6","4.7u","Capacitor_SMD:C_0603_1608Metric","Murata","GRM188R61A475KE15D","Capacitor 4.7 uF X5R 10 V 0603, CP2102N VDD (Silicon Labs CP2102N data sheet Rev. 1.5 Figure 2.3),Capacitor 4.7 uF X5R 10 V 0603, CP2102N VREGIN (Silicon Labs CP2102N data sheet Rev. 1.5 Figure 2.3)","2",""
"C10,C14,C15,C17,C20,C22","4.7u","Capacitor_SMD:C_1206_3216Metric","Murata","GRM31CR71E475KA88L","Capacitor 4.7 uF X7R 25 V 10% 1206, VDD pin 46 (TI SPRS945H 6.9.1.5.1),Capacitor 4.7 uF X7R 25 V 10% 1206, VDD pin 4: CVDD_DECAP 0.1-6.75 uF a pin, CVDD 12-27 uF in all, 4 x 4.7 uF (TI SPRS945H 6.9.1.5.1, Configuration 1 of 6.9.1.3.1.2),Capacitor 4.7 uF X7R 25 V 10% 1206, VDD pin 71 (TI SPRS945H 6.9.1.5.1),Capacitor 4.7 uF X7R 25 V 10% 1206, VDD pin 87 (TI SPRS945H 6.9.1.5.1),Capacitor 4.7 uF X7R 25 V 10% 1206, VREFHIA (pin 25) to VREFLOA (pin 27), internal reference (TI SPRS945H Table 5-1: at least 2.2 uF, as close as possible),Capacitor 4.7 uF X7R 25 V 10% 1206, VREFHIB/C (pin 24) to VREFLOB/C (pin 26) (TI SPRS945H Table 5-1)","6",""
"C13","2.2u","Capacitor_SMD:C_0603_1608Metric","Murata","GRM188R71A225KE15D","Capacitor 2.2 uF X7R 10 V 0603, VDDA pin 11 to VSSA (CVDDA 2.2 uF, TI SPRS945H 6.9.1.5.1, Table 5-1)","1",""
"C16","2.2u","Capacitor_SMD:C_0402_1005Metric","Murata","GRM155R61A225KE01D","Capacitor 2.2 uF X5R 10 V 10% 0402, VDDA pin 34 to VSSA/PGA_GND pins 33 and 32 (TI SPRS945H 6.9.1.5.1, Table 5-1)","1",""
"D1","PMEG6010CEH","Diode_SMD:D_SOD-123F","Nexperia","PMEG6010CEH,115","Schottky 60 V 1 A, VF <= 400 mV at 100 mA, <= 530 mV at 500 mA (Nexperia PMEG6010CEH v.4): a BoosterPack's 5 V cannot reach the USB host","1",""
"D2","PWR","LED_SMD:LED_0603_1608Metric","Kingbright","APTD1608LCGCK","LED green 0603, 3.3 V present (VF 1.9 V typ at 2 mA, DSAO7432)","1",""
"D3","RED","LED_SMD:LED_0603_1608Metric","Kingbright","APTD1608LSURCK","LED red 0603, user LED on GPIO6 (EPWM4A, J4.40)","1",""
"D4","YEL","LED_SMD:LED_0603_1608Metric","Kingbright","APTD1608LSYCK","LED yellow 0603, user LED on GPIO14 (EPWM8A, J4.39)","1",""
"F1","500mA","Fuse:Fuse_1206_3216Metric","Littelfuse","1206L050YR","PTC fuse 0.50 A hold (0.42 A at 40 C), 1.00 A trip, 6 V, R1max 0.70 ohm, 1206 (Littelfuse 1206L)","1",""
"J1","BoosterPack A J1/J3","Connector_PinHeader_2.54mm:PinHeader_2x10_P2.54mm_Vertical","Samtec","SSW-110-23-F-D","Site A BoosterPack J1 (odd pins: J1.1-J1.10, outer) and J3 (even pins: J3.21-J3.30, inner), 2x10 2.54 mm, female, long male leads, as TI's BoosterPack Pinout Standard (Sept 1, 2013) p. 2 asks and recommends","1",""
"J2","BoosterPack A J4/J2","Connector_PinHeader_2.54mm:PinHeader_2x10_P2.54mm_Vertical","Samtec","SSW-110-23-F-D","Site A BoosterPack J4 (odd pins: J4.40 down to J4.31, inner) and J2 (even pins: J2.20 down to J2.11, outer), 2x10 2.54 mm, female, long male leads, as TI's BoosterPack Pinout Standard (Sept 1, 2013) p. 2 asks and recommends","1",""
"J5","BoosterPack B J5/J7","Connector_PinHeader_2.54mm:PinHeader_2x10_P2.54mm_Vertical","Samtec","SSW-110-23-F-D","Site B BoosterPack J5 (odd pins: J5.41-J5.50, outer) and J7 (even pins: J7.61-J7.70, inner), 2x10 2.54 mm, female, long male leads, as TI's BoosterPack Pinout Standard (Sept 1, 2013) p. 2 asks and recommends","1",""
"J6","BoosterPack B J8/J6","Connector_PinHeader_2.54mm:PinHeader_2x10_P2.54mm_Vertical","Samtec","SSW-110-23-F-D","Site B BoosterPack J8 (odd pins: J8.80 down to J8.71, inner) and J6 (even pins: J6.60 down to J6.51, outer), 2x10 2.54 mm, female, long male leads, as TI's BoosterPack Pinout Standard (Sept 1, 2013) p. 2 asks and recommends","1",""
"J9","USB-C","Connector_USB:USB_C_Receptacle_HRO_TYPE-C-31-M-12","Korean Hroparts","TYPE-C-31-M-12","USB-C 2.0 receptacle, 16 pins: power and the CP2102N serial port","1",""
"J10","TI JTAG 14","Connector_PinHeader_2.54mm:PinHeader_2x07_P2.54mm_Vertical","Samtec","TSW-107-07-G-D","TI 14-pin JTAG header, 2x7 0.1 in, pin 6 removed as the key (TI XDS Target Connection Guide; SPRU655I Figure 4): 1 TMS, 2 TRST (open, no TRSTn on the chip), 3 TDI, 4 TDIS, 5 PD, 7 TDO, 9 RTCK = TCK, 11 TCK, 13/14 EMU0/1, 8/10/12 GND","1",""
"JP1","BOOT","Connector_PinHeader_2.54mm:PinHeader_2x02_P2.54mm_Vertical","Samtec","TSW-102-07-G-D","Boot jumpers: 1-2 pulls GPIO24 (boot pin 1) low, 3-4 GPIO32 (boot pin 0); none = flash, 1-2 = SCI, 3-4 = CAN, both = parallel I/O (TI SPRS945H Table 7-13)","1",""
"R1-R3","5.1k","Resistor_SMD:R_0402_1005Metric","","","Resistor 5.1 kohm 1% 0402, USB-C sink Rd on CC1 (TI SLYY228 p. 54: a sink exposes Rd = 5.1 kohm on CC1 and CC2),Resistor 5.1 kohm 1% 0402, USB-C sink Rd on CC2 (TI SLYY228 p. 54: a sink exposes Rd = 5.1 kohm on CC1 and CC2),Resistor 5.1 kohm 1% 0402, VBUS bleed: with the CP2102N divider 4.75 kohm, so up to 185 uA of D1 leakage keeps the bridge's VBUS pin under VIL 0.6 V (Silicon Labs CP2102N data sheet Rev. 1.5 Table 3.7); 1.0 mA from a host","3",""
"R4,R11,R12","680","Resistor_SMD:R_0402_1005Metric","","","Resistor 680 ohm 1% 0402, power LED: (3.3 - 1.9) / 680 = 2.1 mA (Kingbright DSAO7432),Resistor 680 ohm 1% 0402, red LED: (3.3 - 1.75) / 680 = 2.3 mA (Kingbright DSAO7433), inside IOH 4 mA (TI SPRS945H 6.6),Resistor 680 ohm 1% 0402, yellow LED: (3.3 - 1.85) / 680 = 2.1 mA (Kingbright DSAO7434)","3",""
"R5,R8,R9,R13,R14,R31,R32","1k","Resistor_SMD:R_0402_1005Metric","","","Resistor 1 kohm 1% 0402, CP2102N RSTb pull-up to VDD (Silicon Labs CP2102N data sheet Rev. 1.5 2.1),Resistor 1 kohm 1% 0402, CP2102N TXD to GPIO28/SCIA_RX: caps a driver fight at 3.3 mA,Resistor 1 kohm 1% 0402, GPIO11 button: limits a BoosterPack driving J2.17 or J6.57 to 3.3 mA,Resistor 1 kohm 1% 0402, GPIO23 button: limits a BoosterPack driving J2.11 or J6.51 to 3.3 mA,Resistor 1 kohm 1% 0402, GPIO24 boot pull-down through JP1: 0.3 V < VIL 0.8 V with R29 (TI SPRS945H 6.6), 3.3 mA if firmware drives the pin high,Resistor 1 kohm 1% 0402, GPIO29/SCIA_TX to CP2102N RXD: caps a driver fight at 3.3 mA,Resistor 1 kohm 1% 0402, GPIO32 boot pull-down through JP1 (TI SPRS945H 6.6)","7",""
"R6","22.1k","Resistor_SMD:R_0402_1005Metric","","","Resistor 22.1 kohm 1% 0402, CP2102N VBUS divider (Silicon Labs CP2102N data sheet Rev. 1.5 Figure 2.6)","1",""
"R7","47.5k","Resistor_SMD:R_0402_1005Metric","","","Resistor 47.5 kohm 1% 0402, CP2102N VBUS divider: 3.41 V from 5 V (Silicon Labs CP2102N data sheet Rev. 1.5 Figure 2.6, Table 3.7)","1",""
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

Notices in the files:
boards/eos/eos-cm4-base/hardware/eos-cm4-base.kicad_sch:
Copyright (c) 2026 Kartikeydheer Srivastava. Licence: All rights reserved
boards/eos/eos-ra4m2-board/hardware/eos-ra4m2-board.kicad_sch:
Uno R3 relative connector coordinates: Matthew Beckler Arduino Uno R3 dimension drawing v1.05, public domain; facts only.
parts and their libraries:
https://creativecommons.org/licenses/by-sa/4.0
Released under the Creative Commons Attribution Share-Alike 4.0 License
